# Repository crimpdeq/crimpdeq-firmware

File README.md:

# Crimpdeq Firmware

Meet [Crimpdeq](https://crimpdeq.com), a portable digital force sensor designed for climbers, coaches, and therapists to measure and train finger strength, pulling power, and endurance.

Crimpdeq is a fully open-source project: an ESP32-C3 PCB ([KiCad](https://github.com/crimpdeq/crimpdeq-pcb), [tscircuit](https://github.com/crimpdeq/crimpdeq-tscircuit)) with an ADS1220 ratiometric load-cell front end and a MAX17048 fuel gauge, a WH-C100 crane scale, a 3D-printable [case](https://github.com/crimpdeq/crimpdeq-case), and firmware fully written in Rust!

> [!NOTE]
> If you're interested in reproducing this project or giving it a try, please, reach out! You can contact me via email (sergio.gasquez@gmail.com), [Twitter](https://x.com/Sergio_Gasquez) or [Bluesky](https://bsky.app/profile/sergiogasquez.bsky.social).

## Specs

These specs describe PCB V3 with its matching case and firmware. The tscircuit board has the same ADC, fuel gauge and charger, and is not yet validated on hardware.

- Rechargeable battery with USB‑C charging, also while switched off
- Battery level reporting with a MAX17048 fuel gauge
- RGB status LED for connection and low-battery status
- ADS1220 24-bit load-cell ADC
- Communicates via Bluetooth Low Energy (BLE)
- Open-source firmware written in Rust
- Open-source PCB design
- Open-source 3D case design
- Automatic sleep when inactive
- Compatible with Tindeq Progressor app ([Android](https://play.google.com/store/apps/details?id=com.progressor&hl=es_419) | [iOS](https://apps.apple.com/es/app/tindeq-progressor/id1380412428))
- Compatible with Frez app (formerly ClimbHarder) ([Android](https://play.google.com/store/apps/details?id=com.holdtight.climbharder&pcampaignid=web_share) | [iOS](https://apps.apple.com/us/app/climbharder-no-hang-training/id6730120024))
- Sampling frequency: 175 Hz by default, selectable from 20 to 1000 Hz with the Crimpdeq app and kept across reboots
- Linear, quadratic, or two-segment piecewise linear calibration, fitted on the device and selected with the Crimpdeq app (see [Calibration models](calibration/README.md))
- Design load: 1500 N (≈150 kg), full scale
- Precision:
    - 0.05 kg between 0 and 99 kg
    - 0.1 kg between 100 and 150 kg
- Operating temperature: 0–40 °C
- Dimensions: 97 × 77 × 31 mm
- Uses the [Tindeq Progressor API](https://tindeq.com/progressor_api/)

## Firmware Versions

Each PCB revision needs its own firmware; use the latest release for your revision:

| PCB revision | Firmware                                                                      |
| ------------ | ----------------------------------------------------------------------------- |
| V1           | [`v0.4.0`](https://github.com/crimpdeq/crimpdeq-firmware/releases/tag/v0.4.0) |
| V2           | [`v2.1.0`](https://github.com/crimpdeq/crimpdeq-firmware/releases/tag/v2.1.0) |
| V3           | [`v3.0.0`](https://github.com/crimpdeq/crimpdeq-firmware/releases/tag/v3.0.0) |

This firmware targets [crimpdeq-tscircuit `v0.1.0`](https://github.com/crimpdeq/crimpdeq-tscircuit/tree/v0.1.0), which differs from PCB V3 in:

- Load cell E− returns to GND through the ADS1220 low-side switch, so the firmware sets `PSW = 1` and the bridge is only excited while the ADS1220 converts
- ADS1220 DRDY on GPIO0, which the firmware waits on before each read
- MAX17048 I2C on GPIO6 (SDA) and GPIO7 (SCL), swapped from PCB V3
- XL-2121RGBC-2812B status LED, which needs a 0 code high time of at most 300 ns

## Building and Flashing

The [Crimpdeq Book](https://book.crimpdeq.com/) covers assembly, calibration, charging, and general usage. See [Flash with Web Tools](https://book.crimpdeq.com/firmware/web_tools) to flash a release binary and [Flash with Local Setup](https://book.crimpdeq.com/firmware/local) for prerequisites, flashing, and logs.

With the stable Rust toolchain, the `riscv32imc-unknown-none-elf` target, and [`probe-rs`](https://probe.rs/) installed:

```bash
cargo build --release                  # Build only
cargo run --release                    # Build, flash, and start the firmware
DEFMT_LOG=info cargo run --release     # Same, and open the log monitor
```

To try the firmware without a load cell or battery, build it with simulated readings. The mock build runs on the tscircuit board or on an [ESP32-C3 Rust board](https://github.com/esp-rs/esp-rust-board). The load cell repeats pulls that rise from 0 to a peak of up to 30 kg, hold while tiring, and release; calibration reads the weight entered in the app; the battery discharges to 20 % and charges back; and the device logs the idle timeout instead of entering deep sleep:

```bash
cargo run --release --features mock
```

The advertised name, the Progressor ID, and the reported app version come from `DEVICE_NAME`, `DEVICE_ID`, and `DEVICE_VERSION_NUMBER` in [`.cargo/config.toml`](.cargo/config.toml). The calibration (model, curve and points) and the sampling rate are stored in the `calib` and `settings` partitions of [`partitions.csv`](partitions.csv), so erasing the flash also erases the calibration.

The calibration models, their fitting, the flash record and their BLE commands live in the [`calibration`](calibration/README.md) crate, which has no hardware dependencies. Run its tests on the host with:

```bash
cargo test-host
```

## Contributing
Contributions are welcome! Feel free to:
- Submit PRs for bug fixes or new features
- Test and report issues
- Suggest improvements to documentation

## Issues
If you encounter any issue or want to leave any feedback, please [open an issue](https://github.com/crimpdeq/crimpdeq-firmware/issues/new)

## License
This repository is licensed under either of:

- Apache License, Version 2.0 ([LICENSE-APACHE](LICENSE-APACHE) or http://www.apache.org/licenses/LICENSE-2.0)
- MIT license ([LICENSE-MIT](LICENSE-MIT) or http://opensource.org/licenses/MIT)

at your option.

## Kudos
- @bjoernQ for helping me during the development and developing the [`bleps`](https://github.com/bjoernQ/bleps) crate, which the first versions of this firmware were built on.
- [`trouble`](https://github.com/embassy-rs/trouble), the BLE host stack used by this firmware.
- [hangman](https://github.com/kesyog/hangman) for being an improved version of this project and a great source of inspiration for this project.
- Tindeq for having its API public and allowing for projects like this to exist!

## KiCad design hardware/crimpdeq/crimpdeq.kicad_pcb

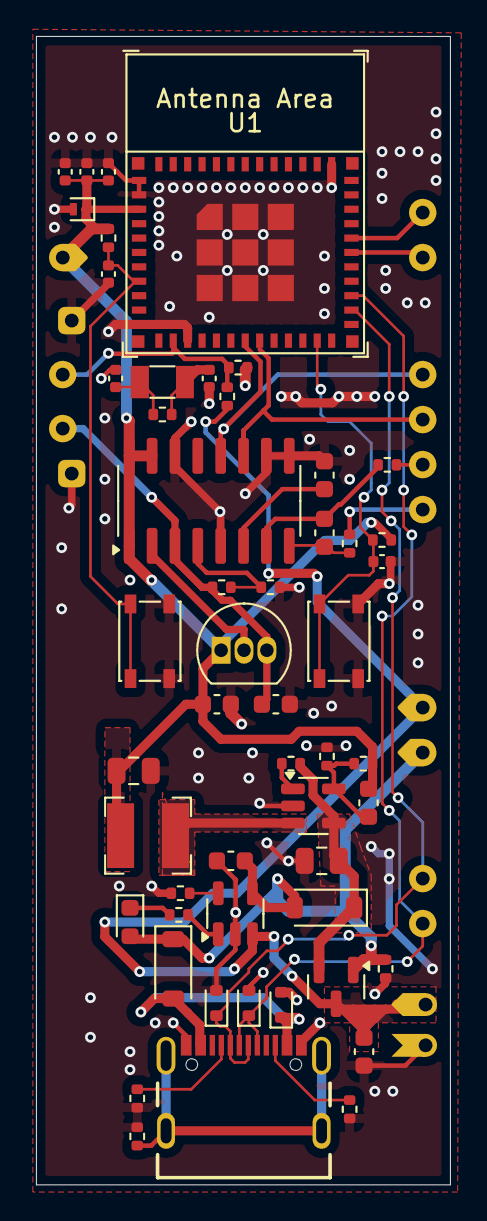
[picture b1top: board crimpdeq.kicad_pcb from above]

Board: 2 copper layers, 23.0 x 63.8 mm, 53 parts (0 on the bottom side), 34 nets.

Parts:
C1, C3: 1uF 16V; C_0402_1005Metric
C2: 100nF 10V; C_0402_1005Metric
C4: 10nF 10V; C_0402_1005Metric
C5, C6: 4.7uF 16V; C_0603_1608Metric
C7, C8: DNP; C_0402_1005Metric
C9, C10: 10uF; C_0603_1608Metric
C11, C12: 0.1uF; C_0603_1608Metric
C14: 1nF 10V; C_0402_1005Metric
C15, C17: 10uF 16V; C_0805_2012Metric
C16: 22pF 50V; C_0603_1608Metric
D1: LED; LED_0603_1608Metric
D2, D8: B5819W; D_SOD-123
D3: LESD8D3.3CAT5G; D_SOD-882
D7, D9, D10: LESD5D5.0CT1G; D_SOD-523
J2: USB4105-GF-A; GCT_USB4105-GF-A
L1: SPH4018H2R2MT (2.2uH 2.2A); L_Bourns-SRN4018
Q1: S8550; TO-92_Inline
Q2: DMG3415U; SOT-23
R1, R2, R10, R11, R14: 10kR 1%; R_0402_1005Metric
R3: 1kR 1%; R_0402_1005Metric
R4: DNP; R_0402_1005Metric
R5: 12kR 1%; R_0402_1005Metric
R6: 8k2R 1%; R_0402_1005Metric
R7, R8: 100R 1%; R_0402_1005Metric
R9, R15: 100kR 1%; R_0402_1005Metric
R12: 33kR 1%; R_0402_1005Metric
R16: 22k1R 1%; R_0402_1005Metric
R17: 0R 1%; R_0402_1005Metric
R18, R19: 5k1R 1%; R_0402_1005Metric
SW1, SW2: SW_Push; SW_SPST_PTS810
U1: ESP32-C3-MINI-1
U2: MCP73831T-2ACI/OT; SOT-23-5
U3: HX711; SOP-16_3.9x9.9mm_P1.27mm
U4: Rust_Board
U6: SY8088; SOT-23-5
Y1: 32.768Hz; Crystal_SMD_3215-2Pin_3.2x1.5mm

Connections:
+3V3: C1.1, C2.1, C4.1, C9.1, C16.1, C17.1, D3.1 (A1), L1.2, Q1.1 (E), R1.1, R10.1, R15.1, U1.3 (3V3), U3.1 (VSUP), U3.15 (RATE), U3.16 (DVDD), U4.1 (3V3)
+5V: C15.1, D2.1 (K), Q2.2 (S), R14.1, U6.4 (IN)
+BATT: C6.1, Q2.3 (D), R12.1, U2.3 (VBAT), U4.11 (VBAT), U4.17 (BAT+)
/Buck_Coil: L1.1, U6.3 (LX)
A+: R7.2, U4.12 (A+)
A-: R8.2, U4.13 (A-)
CHIP_PU: C3.1, R1.2, SW1.1, U1.8 (EN/CHIP_PU)
E+: C10.1, Q1.3 (C), R5.1, U3.3 (AVDD), U4.15 (E+)
ENABLE: R14.2, U6.1 (EN)
GND: C1.2, C2.2, C3.2, C4.2, C5.1, C6.2, C7.2, C8.2, C9.2, C10.2, C11.1, C14.1, C15.2, C17.2, D3.2 (A2), D7.2 (A2), D9.2 (A2), D10.2 (A2), J2.A1_B12 (GND), J2.B1_A12 (GND), R2.1, R6.2, R9.2, R11.2, R16.2, R17.2, R18.2, R19.2, SW1.2, SW2.2, U1.1 (GND), U1.2 (GND), U1.11 (GND), U1.14 (GND), U1.36 (GND), U1.49, U2.2 (VSS), U3.5 (AGND), U3.9 (INB-), U3.10 (INB+), U3.14 (XI), U4.2 (GND), U4.14 (E-), U4.16 (BAT-), U6.2 (GND)
IO0: C7.1, R4.1, Y1.1
IO1: C8.1, R4.2, Y1.2
IO1_ADC: R11.1, R12.2, U1.13 (GPIO1/ADC1_CH1/XTAL_32K_N), U4.3 (A1/GPIO1)
IO4_DATA: U1.18 (GPIO4/ADC1_CH4), U3.12 (DOUT), U4.4 (A4/GPIO4)
IO5_SCK: U1.19 (GPIO5/ADC2_CH0), U3.11 (PD_SCK), U4.5 (A5/GPIO5)
IO9_BOOT: C14.2, R10.2, SW2.1, U1.23 (GPIO9)
IO20_RX: U1.30 (GPIO20/U0RXD), U4.7 (RXD/GPIO20)
IO21_TX: U1.31 (GPIO21/U0TXD), U4.6 (TXD/GPIO21)
unnamed: D1.1 (K), R3.2
unnamed: D8.2 (A), D9.1 (A1), J2.A4_B9 (VBUS), J2.B4_A9 (VBUS)
unnamed: J2.A5 (CC1), R19.1
unnamed: J2.B5 (CC2), R18.1
unnamed: J2.S1 (SHELL_GND), J2.S2 (SHELL_GND), J2.S3 (SHELL_GND), J2.S4 (SHELL_GND), R17.1
unnamed: Q1.2 (B), U3.2 (BASE)
unnamed: R2.2, U2.5 (PROG)
unnamed: R3.1, U2.1 (STAT)
unnamed: C12.1, R7.1, U3.8 (INA+)
unnamed: C12.2, R8.1, U3.7 (INA-)
unnamed: C11.2, U3.6 (VBG)
unnamed: R5.2, R6.1, U3.4 (VFB)
unnamed: C16.2, R15.2, R16.1, U6.5 (FB)
USB_D+: D10.1 (A1), J2.A6 (DP1), J2.B6 (DP2), U1.27 (GPIO19/USB_D+), U4.9 (USB_D+/GPIO19)
USB_D-: D7.1 (A1), J2.A7 (DN1), J2.B7 (DN2), U1.26 (GPIO18/USB_D-), U4.8 (USB_D-/GPIO18)
VBUS: C5.2, D1.2 (A), D2.2 (A), D8.1 (K), Q2.1 (G), R9.1, U2.4 (VDD), U4.10 (VBUS)

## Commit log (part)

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2025-01-28 pcb: Initial placing of hx711
2025-01-29 pcb: Initial wiring of pcb
2025-02-16 docs: Initial readme
2025-02-19 docs: Improve readme
2025-02-19 build: Remove unused deps
2025-02-19 feat: Test esp-hal@1.0.0-beta.0 crates
2025-02-19 build: Update esp-hal revs and enable esp-hal/unstable
2025-02-19 docs: Add a note about disabling defmt
2025-02-19 feat: Add MIT license
2025-02-19 feat: Add Apacahe license
2025-02-19 feat: Update custom runner
2025-02-19 feat: Support soft taring
2025-02-20 feat: Avoid sof taring when taring is done
2025-02-20 feat: Remove lib.rs
2025-02-20 config: Set nightly toolchain for RA
2025-02-20 style: Fix format
2025-02-20 feat: Setup calibration
2025-02-20 feat: Implement calibration
2025-02-20 revert: defmt level
2025-02-20 feat: Update calibration
2025-02-20 chore: Rename method to read_calibrated
2025-02-20 feat: Reduce visibility of methods
2025-02-21 feat: Update constants
2025-02-21 Calibrate the scale (#11)
    * feat: Setup calibration
    * feat: Implement calibration
    * revert: defmt level
    * feat: Update calibration
    * chore: Rename method to read_calibrated
    * feat: Reduce visibility of methods
2025-02-25 build: Update esp-hal crates to released ones
2025-02-25 feat: Remove todos
2025-02-26 pcb: Remove unused exposed pins and connect hx711/RATE to 3.3v
2025-02-26 ci: Dont run Rust CI when updating the pcb
2025-02-26 [PCB]: Remove unused exposed pins and connect hx711/RATE to 3.3v (#15)
    * pcb: Remove unused exposed pins and connect hx711/RATE to 3.3v
    * ci: Dont run Rust CI when updating the pcb
2025-02-26 pcb: Fix DRC unconnected items
2025-02-26 pcb: More DRC fixes
2025-02-27 Create PCB layout (#16)
    * pcb: Remove unused exposed pins and connect hx711/RATE to 3.3v
    * ci: Dont run Rust CI when updating the pcb
    * pcb: Update layout
    * pcb: Fix DRC unconnected items
    * pcb: More DRC fixes
2025-02-27 pcb: DRC issues from PCB layout
2025-02-27 feat: Add KiCad gitignore
2025-02-28 docs: Add shcematic and layout pdfs
2025-02-28 feat: Improve sampling freq
2025-02-28 perf: Avoid having 2 cs
2025-02-28 fix: Typo
2025-03-02 feat: Update taring method
2025-03-02 feat: Simplify taring method
2025-03-02 Improve sampling freq (#18)
    * feat: Improve sampling freq
    * perf: Avoid having 2 cs
    * fix: Typo
    * feat: Update taring method
    * feat: Update calibration
    * feat: Simplify taring method
2025-03-03 feat: Improve taring
2025-03-03 feat: Improve taring (#21)
2025-03-04 docs: Add note
2025-03-07 feat: Improve timestamp (#23)
2025-03-07 feat: Create DeviceState and simplify sending DataPoints
2025-03-07 feat: Simplify bt_task and add ControlOpCode::porcess
2025-03-07 fix: Properly intialize the start_time
2025-03-07 Rearrange modules and fix timestamps (#24)
    * feat: Create DeviceState and simplify sending DataPoints
    * feat: Simplify bt_task and add ControlOpCode::porcess
    * fix: Properly intialize the start_time
2025-03-07 docs: Add some docstrings
2025-03-07 feat: Add NAU7802 library
2025-03-07 feat: Update schematic with NAU7802
2025-03-07 feat: Update layout with NAU7802
2025-03-07 feat: Update pdfs
2025-03-13 feat: Update ESP_WIFI_CONFIG_TICK_RATE_HZ
2025-03-13 feat: Update ESP_WIFI_CONFIG_TICK_RATE_HZ (#25)
2025-03-13 docs: Initial version of the book
2025-03-17 feat: Add battery and calibbration chapters
2025-03-17 Add an mdbook (#26)
    * docs: Initial version of the book
    * feat: Add battery and calibbration chapters
    * ci: Add book CI
2025-03-17 docs: Update readme!
2025-03-17 ci: Fix permissions
2025-03-17 deploy: c01563adc432f97600b05a7acad935196b668876
2025-03-17 ci: Update actions versions
2025-03-18 docs: Update calibration steps
2025-03-19 Remove extra iteration tare loop
    Fix bug: tare loop runs TARING_SAMPLES + 1 iterations
    Solution: remove = from for _ in 0..=TARING_SAMPLES
2025-03-20 docs: Update book
2025-03-21 feat: Allow calibrating via ble
2025-03-21 docs: Updage calibration
2025-03-21 docs: Update calibration instructions
2025-03-21 fix: Format
2025-03-21 docs: Fix format
2025-03-21 feat: Remove ResetCalibration command
2025-03-24 feat: Use an nvs partition to store the calibration
2025-03-25 feat: Add espflash alias
2025-03-25 docs: Update flashing instructions
2025-03-25 feat: Use default nvs partition table
2025-03-25 docs: Update flashing step
2025-03-25 feat: Add a default calibration method
2025-03-25 feat: Add a fallback to default calibration
2025-03-26 feat: Improve ProgressorId response
2025-03-26 feat: Enhance error handling and improve response code documentation
2025-03-26 feat: Update default app version
2025-03-26 fix: Simplify error logging for advertising data creation
2025-03-26 fix: Clippy lint
2025-03-26 fix: Correct typos
2025-03-26 docs: Improve clarity
2025-03-27 fix: Enhance error handling in calibration and advertising data processes
2025-03-27 feat: Update gitignore
2025-03-27 docs: Add badges
2025-03-27 feat: Update debug logs
2025-03-28 feat: Initial tests
2025-03-29 fix: ProgressorId len
2025-03-31 feat: Use trouble instead of bleps
2025-03-31 feat: Stop sending measurements if the app is closed
2025-03-31 feat: Small improvements
2025-03-31 feat: Create ble module and reorganize methods
2025-03-31 feat: Send a hardcoded battery level
2025-03-31 feat: Send only the required bytes
2025-03-31 feat: Allow specifying the id in hex format
2025-03-31 feat: Improvements and code cleanups
2025-04-01 feat: Remove SoftTare
2025-04-01 docs: Update code structure
2025-04-01 feat: Add release proccess
2025-04-01 feat: Use device name for BLE advertising and implement random BLE address generation
2025-04-01 build: Update deps and remove unused
2025-04-01 fix: Remove unused comment
2025-04-02 build: Remove unused features
2025-04-02 Code cleanups (#34)
    * build: Update deps and remove unused
    * fix: Remove unused comment
    * build: Remove unused features
2025-04-03 feat: Improve DEVICE_ID parsing
2025-04-03 pcb: Update hx711 schematic according to the datasheet
2025-04-24 feat: Generate gerber files
2025-04-24 feat: Regenerate production files
2025-04-24 Update hx711 schematic according to the datasheet (#35)
    * pcb: Update hx711 schematic according to the datasheet
    * feat: Generate gerber files
    * feat: Regenerate production files
2025-05-08 docs: Improve how to optimize hx711
2025-05-16 feat: Remove book
2025-05-16 feat: Remove book ci
2025-05-27 feat: Remove calibration offset
2025-06-03 build: Update esp-hal deps to test 1.0.0-beta.1
2025-06-03 build: Use released deps
2025-06-03 Update deps to esp-hal@1.0.0 beta.1 releases (#37)
    * build: Update esp-hal deps to test 1.0.0-beta.1
    * build: Use released deps
2025-06-03 feat: Tare the scale when initializing it
2025-06-03 feat: Clippy lints
2025-07-01 feat: Test ble rates
2025-07-04 Remove calibration offset (#38)
    * feat: Remove calibration offset
    * feat: Tare the scale when initializing it
    * feat: Clippy lints
2025-07-04 build: Update trouble-host
2025-08-06 build: Update esp-hal to latest releases
2025-09-05 build: Remove patches
2025-10-09 feat: Add app descriptor
2025-10-09 format: Remove unnecesary parenthesis
2025-10-09 build: Update deps
2025-10-09 feat: Update deps to latest esp-hal rev
2025-10-09 build: Remover esp-println
2025-10-09 feat: Remove unnecesary defmt::Debug2Format calls
2025-10-13 build: Update trouble
2025-10-13 fix: Lints
2025-10-13 docs: Update frez name
2025-10-13 build: Use released crates
2025-10-14 feat: Remove unnecesary config
2025-10-14 Update dependencies to latest `esp-hal@1.0.0-rc.1` (#42)
    * build: Update deps
    * feat: Update how we handle flash
    * feat: Update deps to latest esp-hal rev
    * build: Remover esp-println
    * feat: Remove unnecesary defmt::Debug2Format calls
    * build: Update trouble
2025-10-15 feat: Reduce the memory used
2025-10-21 feat: Allow writting
2025-11-04 build: Update to esp-hal@1.0.0
2025-11-21 feat: Implement battery voltage reading
2025-11-24 feat: Average battery voltage readings over multiple samples
2025-11-25 fix: Use u32 to avoid overflow
2025-12-19 feat: Minor improvements
2025-12-19 feat: Put the device in deepsleep if it doesnt connect in 5 mins
2025-12-29 Add battery voltage reading and deep sleep support (#43)
    * feat: Implement battery voltage reading
    * feat: Average battery voltage readings over multiple samples
    * fix: Use u32 to avoid overflow
    * feat: Put the device into deep_sleep after 5 mins of ble disconnected
    * feat: Minor improvements
    * feat: Put the device in deepsleep if it doesnt connect in 5 mins
2025-12-30 chore: Delete assets and hardware folder
2025-12-30 docs: Update readme
2025-12-30 build: Bump versions
2025-12-30 chore: Update Rust configuration and VSCode settings
2025-12-31 ci: Update funding
2026-01-05 docs: Fix typo
2026-01-05 fix: Typo and redability
2026-02-06 build: Bump Rust edition
2026-02-06 fix: Heap allocation and clippy lints
2026-02-08 fix: Remove unnecesary probe-rs arg and avoid double CI run
2026-02-08 Support multi-point calibration
2026-02-09 Support multi-point calibration with stored points
2026-02-09 feat: Update logs
2026-02-10 style: Cargo fmt
2026-02-10 Support multi-point calibration, store points, and log points and send to app on GetCalibration (#46)
    * Support multi-point calibration with stored points
    * style: Cargo fmt
2026-02-10 Support multi-point calibration, store points, and log points and send to app on GetCalibration (#46) (#47)
    * Support multi-point calibration with stored points
    * style: Cargo fmt
2026-02-10 feat: Update tindeq API
2026-02-11 fix: Format and rebase
2026-02-12 feat: Report calibration values
2026-02-12 refactor: Remove unused tared field and simplify measurement state management
2026-02-12 feat: Bump crimpdeq version
2026-02-13 Add calibration report for Crimpdeq app (#49)
    * feat: Report calibration values
    * refactor: Remove unused tared field and simplify measurement state management
    * feat: Bump crimpdeq version
2026-02-16 feat: Update default calibration
2026-02-23 feat: Update device version number
2026-02-25 docs: Update links
2026-02-27 feat: Upload merged bin to releases
2026-03-03 fix: malformed scan response payload likely breaks UUID discovery
2026-03-04 refactor: Simplify DeviceState initialization with a new constructor
2026-03-04 feat: Improve advertising
2026-03-04 feat: Remove DEVICE_ID duplications
2026-03-04 feat: Add partition table and update calibration storage handling
2026-03-04 feat: Enhance calibration handling and improve control command responses
2026-03-05 perf: batch weight measurements in BLE notifications
2026-03-05 fix: avoid persisting temporary calibration factor
2026-03-05 fix: avoid panic on oversized BLE advertising payload
2026-03-05 ci: use custom partition table in release images
2026-03-05 fix: add timeout and retries for HX711 ready wait
2026-03-05 fix: validate device id and derive BLE address from it
2026-03-05 fix: tighten calibration command parsing and cleanup state handling
2026-03-05 fix: report runtime calibration factor in get calibration
2026-03-05 fix: prioritize control responses and harden calibration checks
2026-03-05 feat: Decrease CPU freq
2026-03-06 feat: add low-power shutdown handling
2026-03-27 feat: Mock measurements
2026-03-31 fix: correct ble scan response
2026-03-31 fix: harden sensor and command handling
2026-03-31 fix: clear queued notifications on reconnect
2026-04-13 fmt: FIx cargo fmt
2026-04-13 Fix BLE advertising and harden sensor handling (#50)
    * fix: correct ble scan response
    * fix: harden sensor and command handling
    * fix: clear queued notifications on reconnect
    * fmt: FIx cargo fmt
2026-04-15 build: Update deps to esp-hal@1.1
2026-04-16 feat: Make the ble connection more reliable
2026-04-16 feat: batch weight samples in BLE packets
2026-04-23 feat: Update default calibration factor
2026-04-24 fix: improve idle sleep behavior
2026-04-24 build: add cargo flash alias
2026-05-01 perf: avoid cloning measurement batches
2026-05-01 build: Use esp-hal@1.1.0
2026-06-03 build: Update esp-radio@1.0.0-beta.0
2026-06-29 feat: add ws2812b status led
2026-06-29 fix: reset state on shutdown command
2026-06-29 feat: use max17048 battery gauge
2026-06-30 fix: correct battery gauge pin mapping
2026-06-30 build: update smartled git source
